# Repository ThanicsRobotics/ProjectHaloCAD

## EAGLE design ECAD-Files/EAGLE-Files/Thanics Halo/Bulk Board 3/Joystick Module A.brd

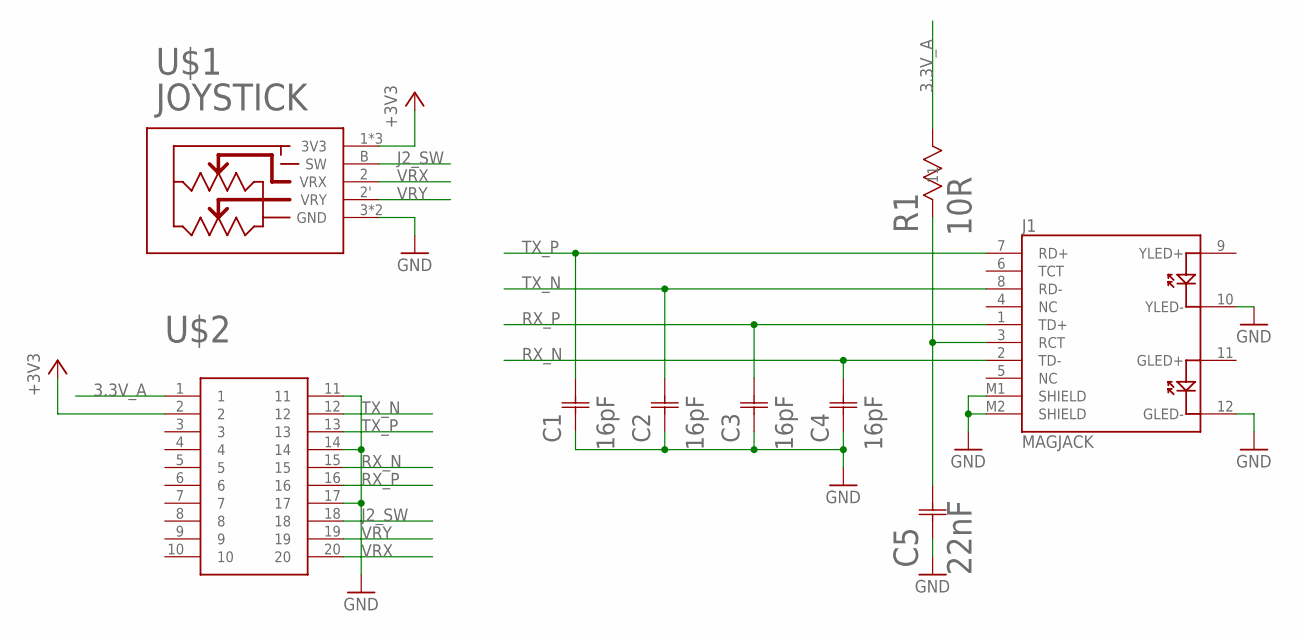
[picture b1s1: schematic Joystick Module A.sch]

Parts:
C1, C2, C3, C4: 16pF; G-155-M
C5: 22nF; G-155-M
J1: MAGJACK
R1: 10R; STA_RNCP0805-M
U$1: JOYSTICK"; JOYSTICK
U$2: EDGE_CONNECTOR_20POS_CONTACTS

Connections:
3.3V_A: R1.2 (22), U$2.1
+3V3: U$1.1 (3V3), U$1.1' (3V3), U$1.A (3V3), U$2.2
GND: C1.1 (11), C2.1 (11), C3.1 (11), C4.1 (11), C5.1 (11), J1.10 (YLED-), J1.12 (GLED-), J1.M1 (SHIELD), J1.M2 (SHIELD), U$1.3 (GND), U$1.3' (GND), U$2.11, U$2.14, U$2.17
J2_SW: U$1.B (SW), U$2.18
unnamed: C5.2 (22), J1.3 (RCT), R1.1 (11)
RX_N: C4.2 (22), J1.2 (TD-), U$2.15
RX_P: C3.2 (22), J1.1 (TD+), U$2.16
TX_N: C2.2 (22), J1.8 (RD-), U$2.12
TX_P: C1.2 (22), J1.7 (RD+), U$2.13
VRX: U$1.2 (VRX), U$2.20
VRY: U$1.2' (VRY), U$2.19

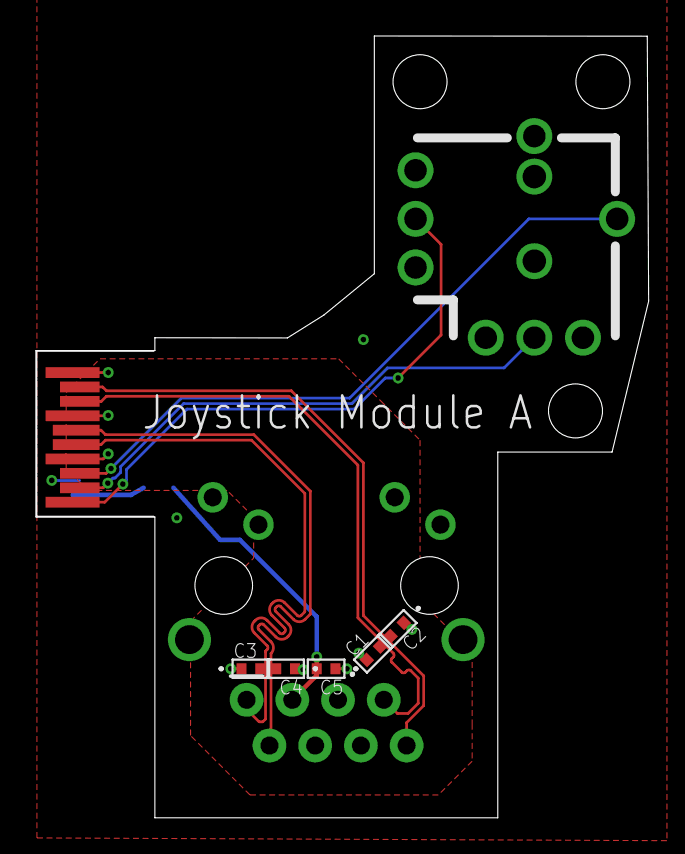
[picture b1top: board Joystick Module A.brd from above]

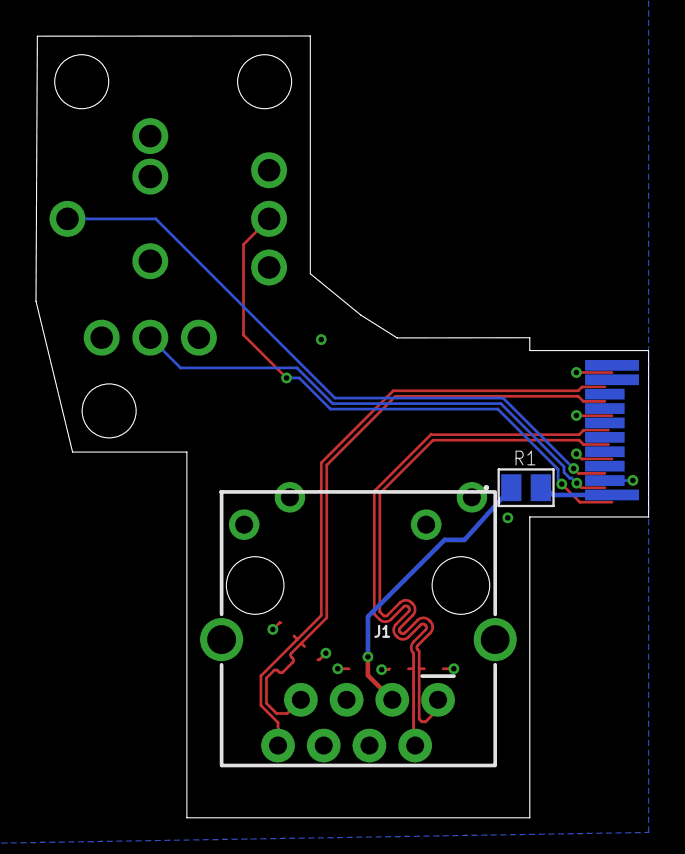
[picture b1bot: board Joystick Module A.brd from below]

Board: 4 copper layers, 34.0 x 43.4 mm, 9 parts (2 on the bottom side), 11 nets.

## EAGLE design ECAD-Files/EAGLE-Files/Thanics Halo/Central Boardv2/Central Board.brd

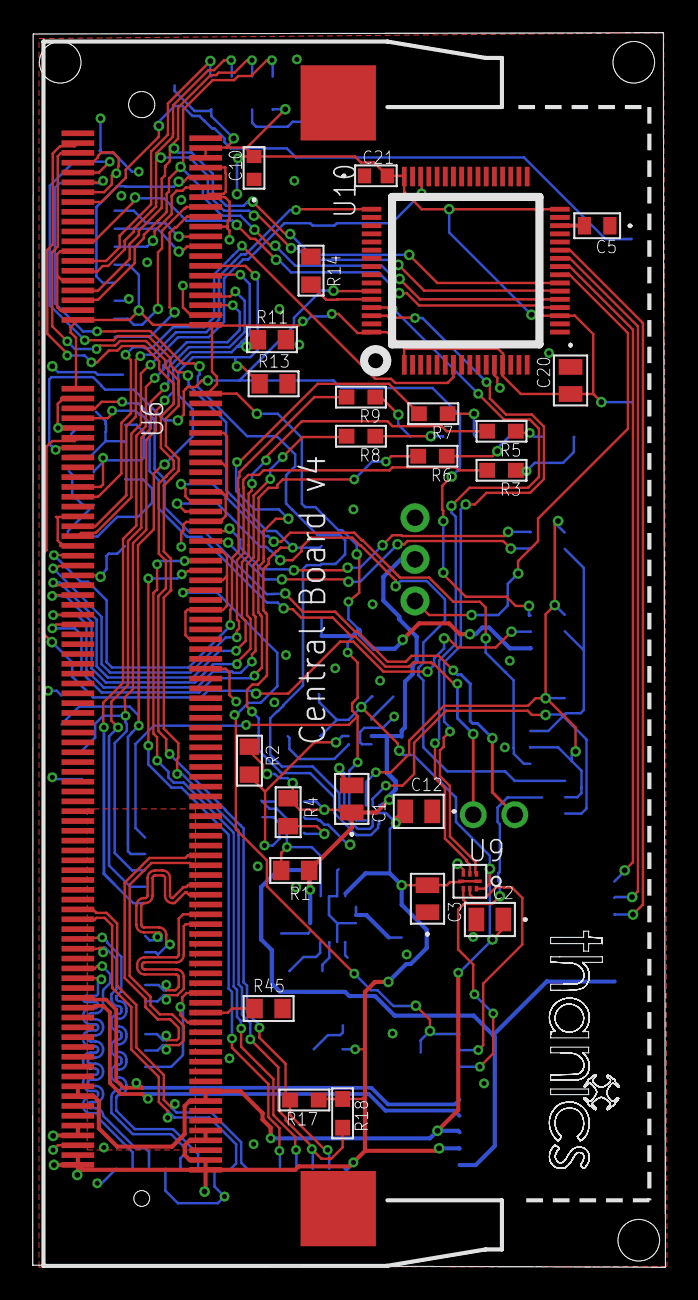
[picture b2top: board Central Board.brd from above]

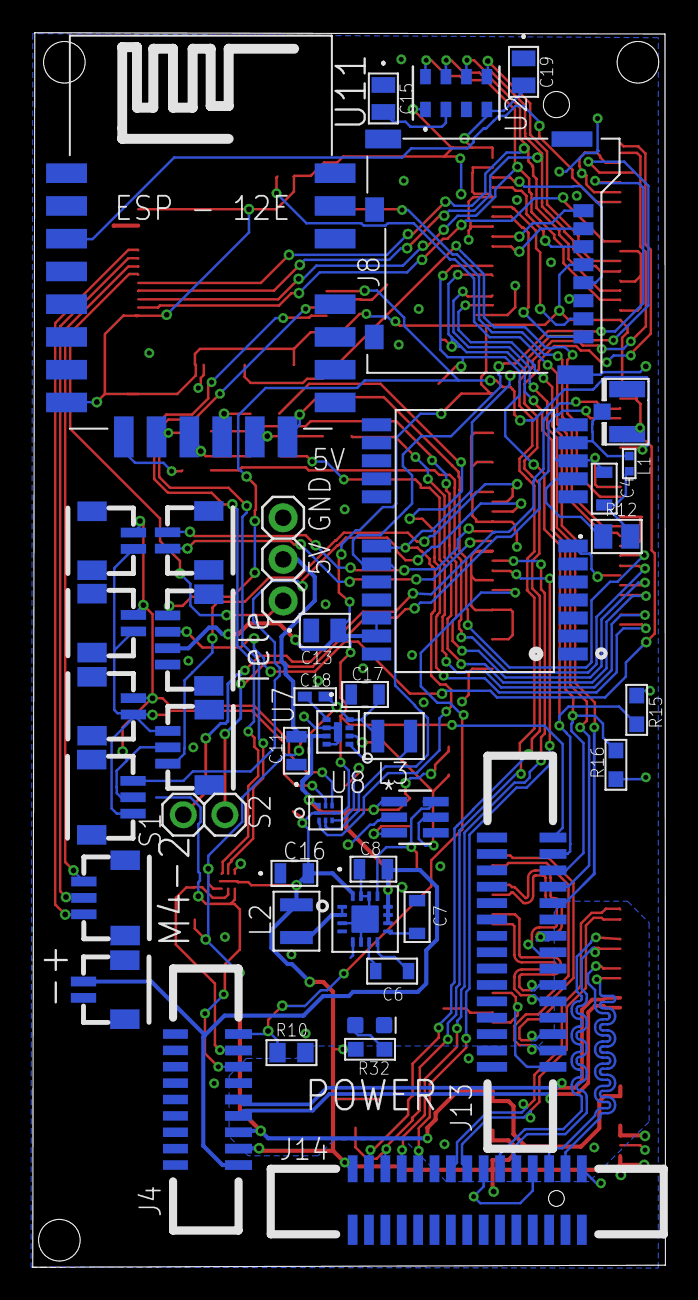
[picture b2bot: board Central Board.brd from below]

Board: 4 copper layers, 38.6 x 75.4 mm, 69 parts (43 on the bottom side), 91 nets.

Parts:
C1, C2, C3, C12, C13, C20: 0.1uF; 0805
C4, C6, C7: 10nF; 0603_CAPACITOR
C5: 4.7uF; 0603-M
C8, C11, C17: 10uF; G-21
C10, C21: 2.2uF; G-188-M
C15, C19: 1uF; YAG_CC0805
C16: 22uF; G-21
C18: 560pF; CC0402N-M
D1: GREEN; LED-0603
J1, J2, J6, J7, J9: JST_SH_2POS
J3: JST_SH_4POS
J4: 9POS_FFC_CONNECTOR
J5: U.FL
J8: MICROSD
J10, J11, J12: JST_SH_3POS
J13, J14: 15POS_FFC_CONNECTOR
JP1: 1X02
JP2: 1X03
L1: 27 nH; 0402_INDUCTOR
L2, L3: 470nH; 1008_INDUCTOR
R1, R2, R4, R10, R11, R13, R14, R45: 10k; RC0805N
R3, R5, R6, R7, R8, R9, R32: 20R; RC0603N-M
R12: 10; STA_RNCP0805-M
R15, R16, R17, R18: 1k; RC0603N-M
U2: LGA8-M
U3: LM3880MF-1AA/NOPBMF06A-M; MF06A-M
U4: NEO-M8
U5: TPS6209; VQFN16
U6: SO-DIMM
U7: MIC23050; MLF(ML)_8PIN
U8, U9: 8-UMLP
U10: LQFP64
U11: ESP12E-SMD

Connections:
1.8V: C2.1, C17.2, C18.2, J4.3, L3.P$2, U6.183, U6.184, U6.185, U6.186, U7.4, U9.8
+3V3: C3.2, C10.2, C12.2, C13.2, C16.2, C19.2, C20.2, C21.2, J3.3, J4.2, J8.4, J13.15, J14.15, L2.P$2, R15.1, R16.1, R17.1, R18.1, R32.2, U2.1, U2.4, U4.22, U4.23, U5.16, U6.4, U6.6, U6.39, U6.40, U6.41, U6.42, U6.191, U6.192, U6.193, U6.194, U6.197, U6.198, U6.199, U6.200, U8.1, U8.5, U9.1, U9.5, U10.1, U10.13, U10.19, U10.32, U10.48, U10.64, U11.VCC
+5V: C1.1, C8.2, C11.2, J4.1, J6.1, JP2.2, R1.1, R2.1, R4.1, U3.1, U5.10, U5.11, U5.12, U7.7, U8.8
C0_C_N: J13.8, U6.144
C0_C_P: J13.9, U6.142
C0_D0_N: J13.2, U6.138
C0_D0_P: J13.3, U6.136
C0_D1_N: J13.5, U6.150
C0_D1_P: J13.6, U6.148
C0_IO0: J13.11, U6.36
C0_IO1: J13.12, U6.34
C1_C_N: J14.8, U6.149
C1_C_P: J14.9, U6.147
C1_D0_N: J14.2, U6.161
C1_D0_P: J14.3, U6.159
C1_D1_N: J14.5, U6.155
C1_D1_P: J14.6, U6.153
C1_IO0: J14.11, U6.78
C1_IO1: J14.12, U6.76
GND: C1.2, C2.2, C3.1, C4.1, C5.1, C7.1, C8.1, C10.1, C11.1, C12.1, C13.1, C15.1, C16.1, C17.1, C19.1, C20.1, C21.1, D1.C, J3.4, J4.6, J5.P$1, J5.P$2, J6.2, J8.6, J8.9, J8.10, J8.11, J8.12, J8.13, J13.1, J13.4, J13.7, J13.10, J14.1, J14.4, J14.7, J14.10, JP2.3, R10.2, R11.2, R13.2, R14.1, R45.2, U2.3, U3.2, U4.7, U4.10, U4.12, U4.13, U4.24, U5.3, U5.5, U5.6, U5.14, U5.15, U5.17, U6.1, U6.7, U6.8, U6.13, U6.14, U6.19, U6.20, U6.25, U6.26, U6.31, U6.32, U6.37, U6.38, U6.43, U6.44, U6.49, U6.50, U6.55, U6.56, U6.61, U6.62, U6.67, U6.68, U6.73, U6.74, U6.79, U6.80, U6.85, U6.86, U6.91, U6.92, U6.97, U6.98, U6.103, U6.104, U6.109, U6.110, U6.115, U6.116, U6.121, U6.122, U6.127, U6.133, U6.134, U6.139, U6.140, U6.145, U6.146, U6.151, U6.152, U6.157, U6.163, U6.164, U6.169, U6.170, U6.181, U6.182, U6.187, U6.188, U6.195, U6.196, U6.G1, U6.G2, U7.6, U7.8, U7.EP, U8.4, U9.4, U10.12, U10.18, U10.31, U10.47, U10.63, U11.GND
GPCLK1: J4.9, R10.1, U6.82
I2C_MPU_SCL: U9.3, U10.61
I2C_MPU_SDA: U9.2, U10.62
I2C_SCL: U4.19, U6.11, U8.3
I2C_SCL_1V8: J4.7, U9.6
I2C_SCL_5V: J1.2, J2.2, J7.2, J10.2, J11.2, U8.6
I2C_SDA: U4.18, U6.9, U8.2
I2C_SDA_1V8: J4.8, U9.7
I2C_SDA_5V: J1.1, J2.1, J7.1, J10.1, J11.1, U8.7
ID_SD: U6.15, U11.CH_PD
INT_A: J10.3, U6.64
INT_B: J11.3, U6.66
MOTOR1: JP2.1, U10.24
MOTOR2: J12.1, U10.25
MOTOR3: J12.2, U10.26
MOTOR4: J12.3, U10.27
unnamed: J5.P$3, L1.P$1, U4.11
unnamed: C6.2, U5.7
unnamed: C6.1, U5.8
unnamed: D1.A, R32.1
unnamed: R1.2, U3.6, U5.13
unnamed: R2.2, U3.5, U7.2
unnamed: R3.1, U11.CS0
unnamed: R5.1, U11.MISO
unnamed: R6.1, U11.GPIO9
unnamed: R7.1, U11.GPIO10
unnamed: C5.2, U10.30
unnamed: C15.2, U2.2
unnamed: R12.1, U4.9
unnamed: R8.1, U11.MOSI
unnamed: R9.1, U11.SCLK
unnamed: R14.2, U10.60
unnamed: C4.2, L1.P$2, R12.2
unnamed: C7.2, U5.9
unnamed: L2.P$1, U5.1, U5.2
unnamed: L3.P$1, U7.1
unnamed: C18.1, U7.5
unnamed: R45.1, U6.168
NRST: U6.63, U10.7
POWER_SEQ_EN: R4.2, U3.3
SCL0: J13.13, R11.1, R16.2, U6.30
SCL1: J14.13, R18.2, U6.5
SDA0: J13.14, R13.1, R15.2, U6.28
SDA1: J14.14, R17.2, U6.3
SDX_CLK: J8.5, U6.10
SDX_CMD: J8.3, U6.12
SDX_D0: J8.7, U6.16
SDX_D1: J8.8, U6.18
SDX_D2: J8.1, U6.22
SDX_D3: J8.2, U6.24
SD_CLK: R9.2, U6.75
SD_CMD: R3.2, U6.77
SD_D0: R5.2, U6.81
SD_D1: R8.2, U6.83
SD_D2: R6.2, U6.87
SD_D3: R7.2, U6.89
SERVO1: JP1.1, U6.45
SERVO2: JP1.2, U6.47
SPI_CS0: U2.5, U6.27
SPI_CS1: U6.23, U10.20
SPI_MISO: U2.6, U6.29, U10.22
SPI_MOSI: U2.7, U6.33, U10.23
SPI_SCLK: U2.8, U6.35, U10.21
SWCLK: U6.69, U10.49
SWDIO: U6.71, U10.46
UART2_RX: J9.2, U6.72
UART2_TX: J9.1, U6.70
USART1_RX: J3.1, U6.53, U10.59
USART1_TX: J3.2, U6.51
USB_D_N: J4.4, U6.167
USB_D_P: J4.5, U6.165

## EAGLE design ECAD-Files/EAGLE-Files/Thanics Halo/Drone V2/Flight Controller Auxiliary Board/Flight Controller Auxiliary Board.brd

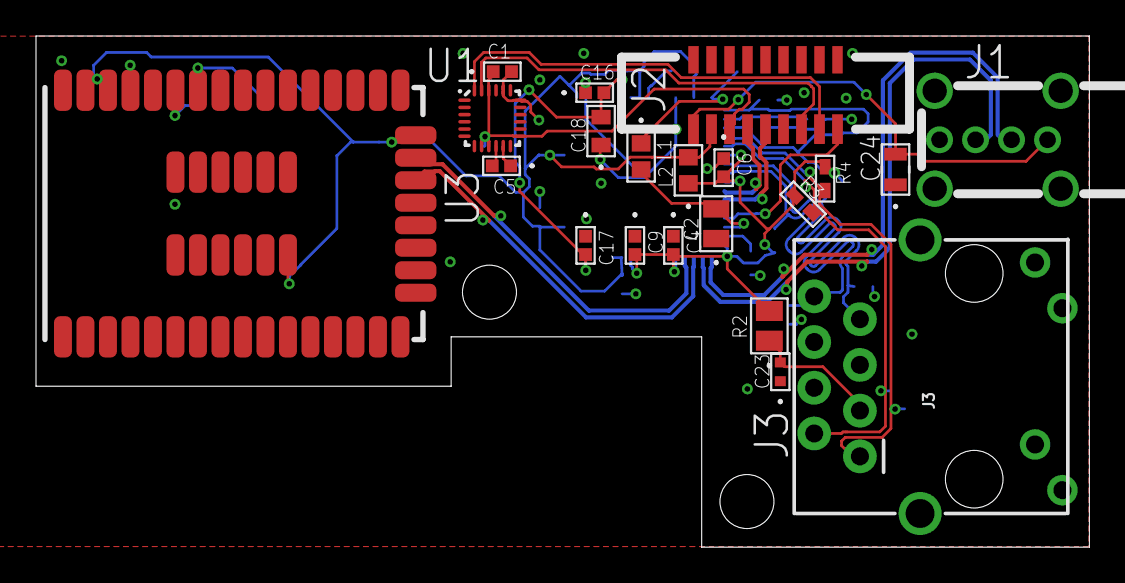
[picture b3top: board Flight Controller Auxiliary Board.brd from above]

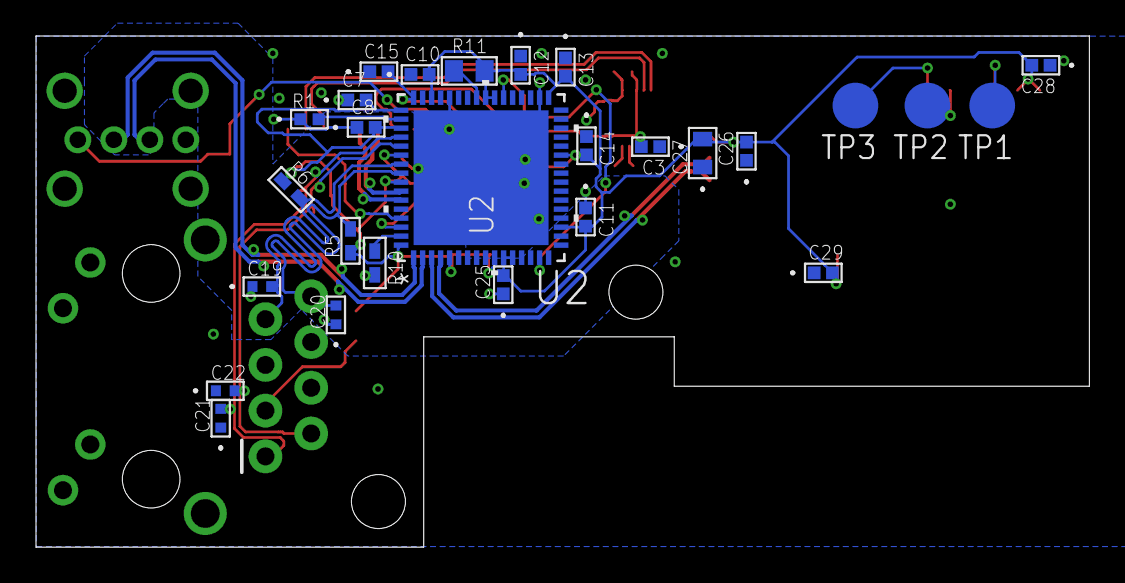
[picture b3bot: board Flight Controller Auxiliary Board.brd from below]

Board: 4 copper layers, 58.5 x 28.4 mm, 48 parts (27 on the bottom side), 29 nets.

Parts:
C1, C3, C4, C5, C6, C7, C8, C9, C10, C11, C12, C13, C14, C15, C16, C17, C25, C26, C28, C29: 0.1uF; 0402-M
C2: 1uF; YAG_CC0805
C18, C27: 4.7uF; 0603-M
C19, C20, C21, C22: 16pF; G-155-M
C23: 22nF; G-155-M
C24: 22uF; G-21
J1: USB_A_VERTICAL
J2: 9POS_FFC_CONNECTOR
J3: MAGJACK
L1, L2: FB; IND_BLM18_0603-M
R1: 12.4k; YAG_R0402-M
R2: 10R; STA_RNCP0805-M
R3, R4, R5, R6: 49R9; RC0402N-M
R10: 12k; RC0402N-M
R11: 10k; RC0805N
TP1, TP2, TP3: TPB2,54; B2,54
U1: QFN40P300X300X105-25N
U2: QFN64_9X9MC-M
U3: WGM110A

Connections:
1.8V: C1.1, C3.2, J2.3, U1.8, U1.9, U1.13, U1.22
3.3V_A: C4.2, C6.2, C7.2, C8.2, C9.2, L2.1, R2.2, R3.1, R4.1, R5.1, R6.1, U2.5, U2.10, U2.49, U2.51, U2.54, U2.57, U2.64
+3V3: C10.2, C11.2, C12.2, C13.2, C14.2, C25.2, C26.2, C27.2, C28.2, C29.2, J2.2, L2.2, R11.2, U2.11, U2.12, U2.19, U2.27, U2.33, U2.39, U2.40, U2.46, U3.24, U3.38, U3.39, U3.51
+5V: C24.2, J1.1, J2.1
GND: C1.2, C2.1, C3.1, C4.1, C5.1, C6.1, C7.1, C8.1, C9.1, C10.1, C11.1, C12.1, C13.1, C14.1, C15.1, C16.1, C17.1, C18.1, C19.1, C20.1, C21.1, C22.1, C23.1, C24.1, C25.1, C26.1, C27.1, C28.1, C29.1, J1.4, J1.P$5, J1.P$6, J1.P$7, J1.P$8, J2.6, J3.10, J3.12, J3.M1, J3.M2, R1.1, R10.2, U1.11, U1.18, U1.20, U2.34, U2.44, U2.65, U3.1, U3.16, U3.25, U3.40, U3.42, U3.44, U3.46, U3.48
GPCLK: J2.9, U2.61
unnamed: R11.1, U2.41
unnamed: R10.1, U2.63
unnamed: C15.2, L1.1, U2.48
unnamed: C2.2, L1.2, U2.62
unnamed: TP1.TP, U3.37
unnamed: TP2.TP, U3.35
unnamed: TP3.TP, U3.34
unnamed: C5.2, U1.10
unnamed: R1.2, U2.50
unnamed: C16.2, C17.2, C18.2, U2.15, U2.38
unnamed: C23.2, J3.3, R2.1
RX_N: C22.2, J3.2, R3.2, U2.53
RX_P: C21.2, J3.1, R4.2, U2.52
SCL: J2.7, U1.23
SDA: J2.8, U1.24
TX_N: C20.2, J3.8, R5.2, U2.56
TX_P: C19.2, J3.7, R6.2, U2.55
USB_D2_N: J1.2, U2.1
USB_D2_P: J1.3, U2.2
USB_D3_N: U2.3, U3.22
USB_D3_P: U2.4, U3.23
USB_D_N: J2.4, U2.58
USB_D_P: J2.5, U2.59

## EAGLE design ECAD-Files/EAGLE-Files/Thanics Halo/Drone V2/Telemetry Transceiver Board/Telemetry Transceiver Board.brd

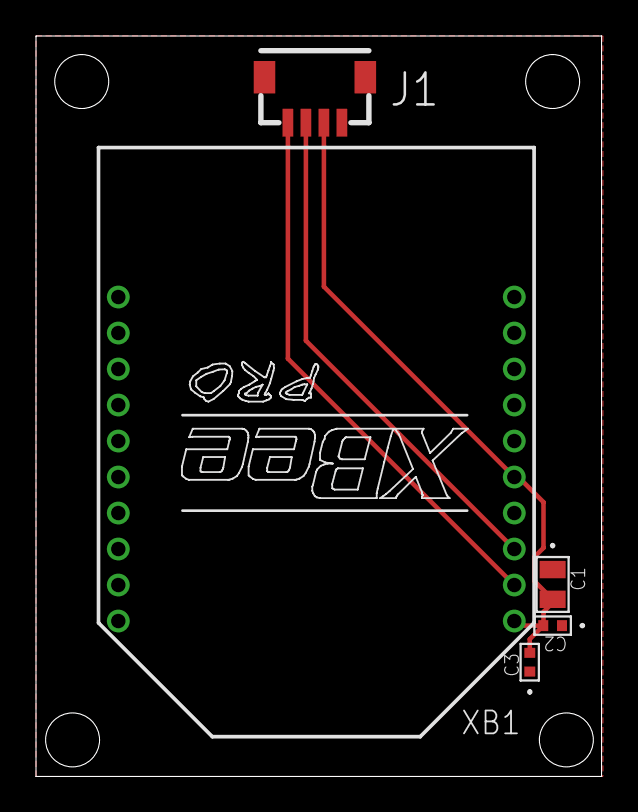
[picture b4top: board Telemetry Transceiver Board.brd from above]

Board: 2 copper layers, 31.4 x 41.1 mm, 5 parts (0 on the bottom side), 4 nets.

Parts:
C1: 1uF; YAG_CC0805
C2, C3: 16pF; G-155-M
J1: JST_SH_4POS
XB1: XBEE-PRO

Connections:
+3V3: C1.2, C2.2, C3.2, J1.3, XB1.1, XB1.5
GND: C1.1, C2.1, C3.1, J1.4, XB1.10, XB1.14
RX: J1.2, XB1.3
TX: J1.1, XB1.2

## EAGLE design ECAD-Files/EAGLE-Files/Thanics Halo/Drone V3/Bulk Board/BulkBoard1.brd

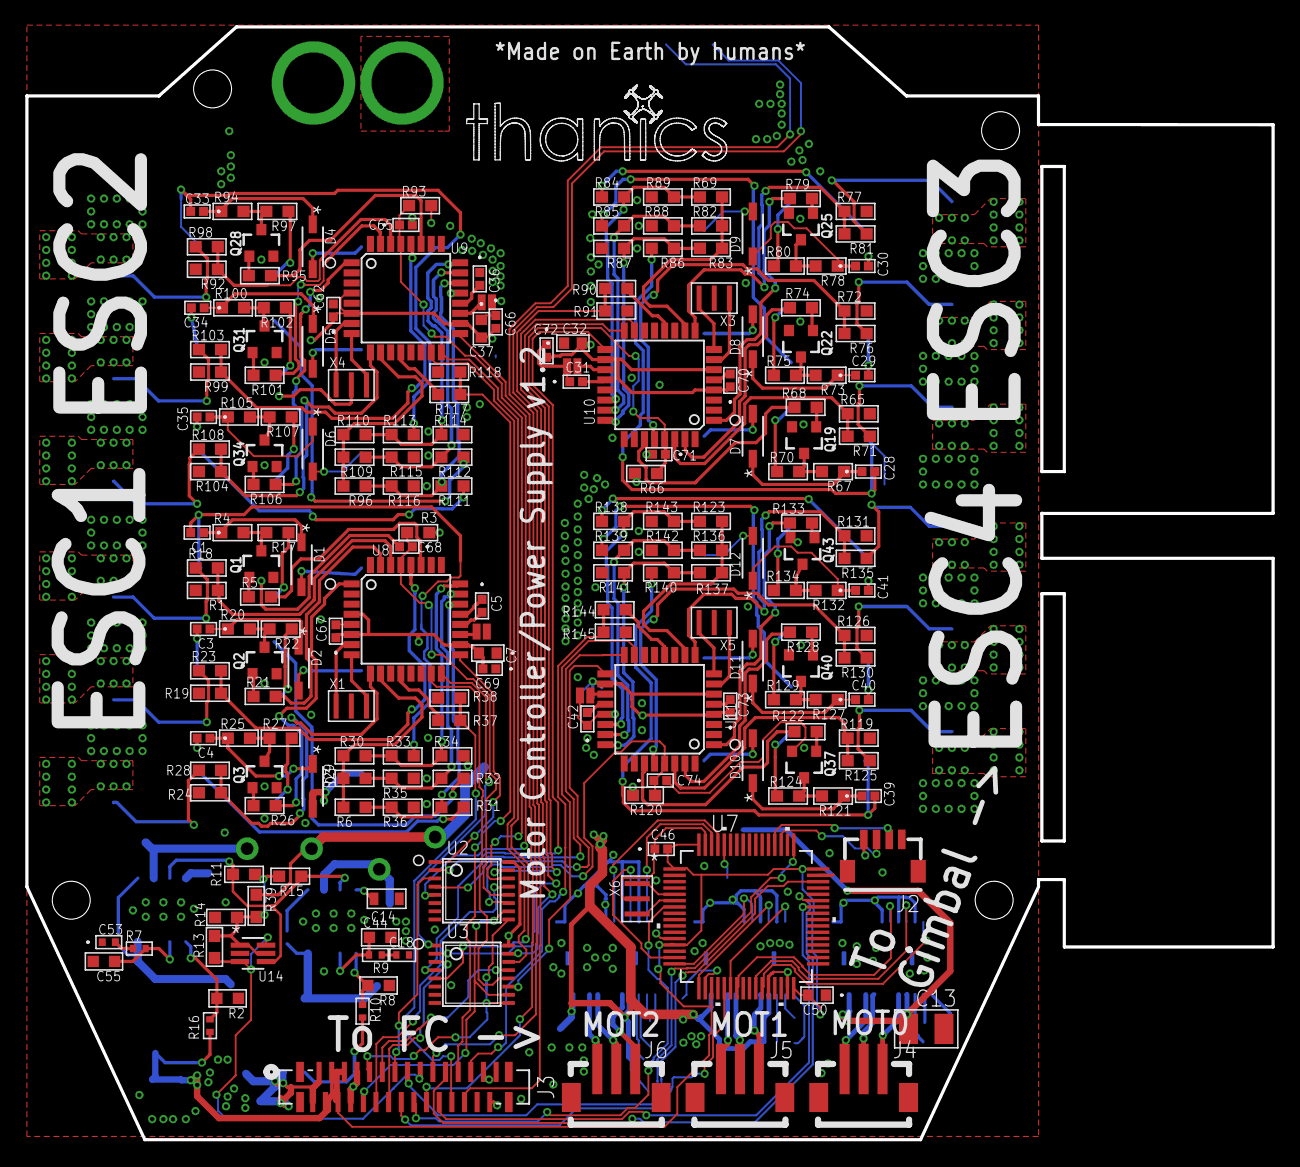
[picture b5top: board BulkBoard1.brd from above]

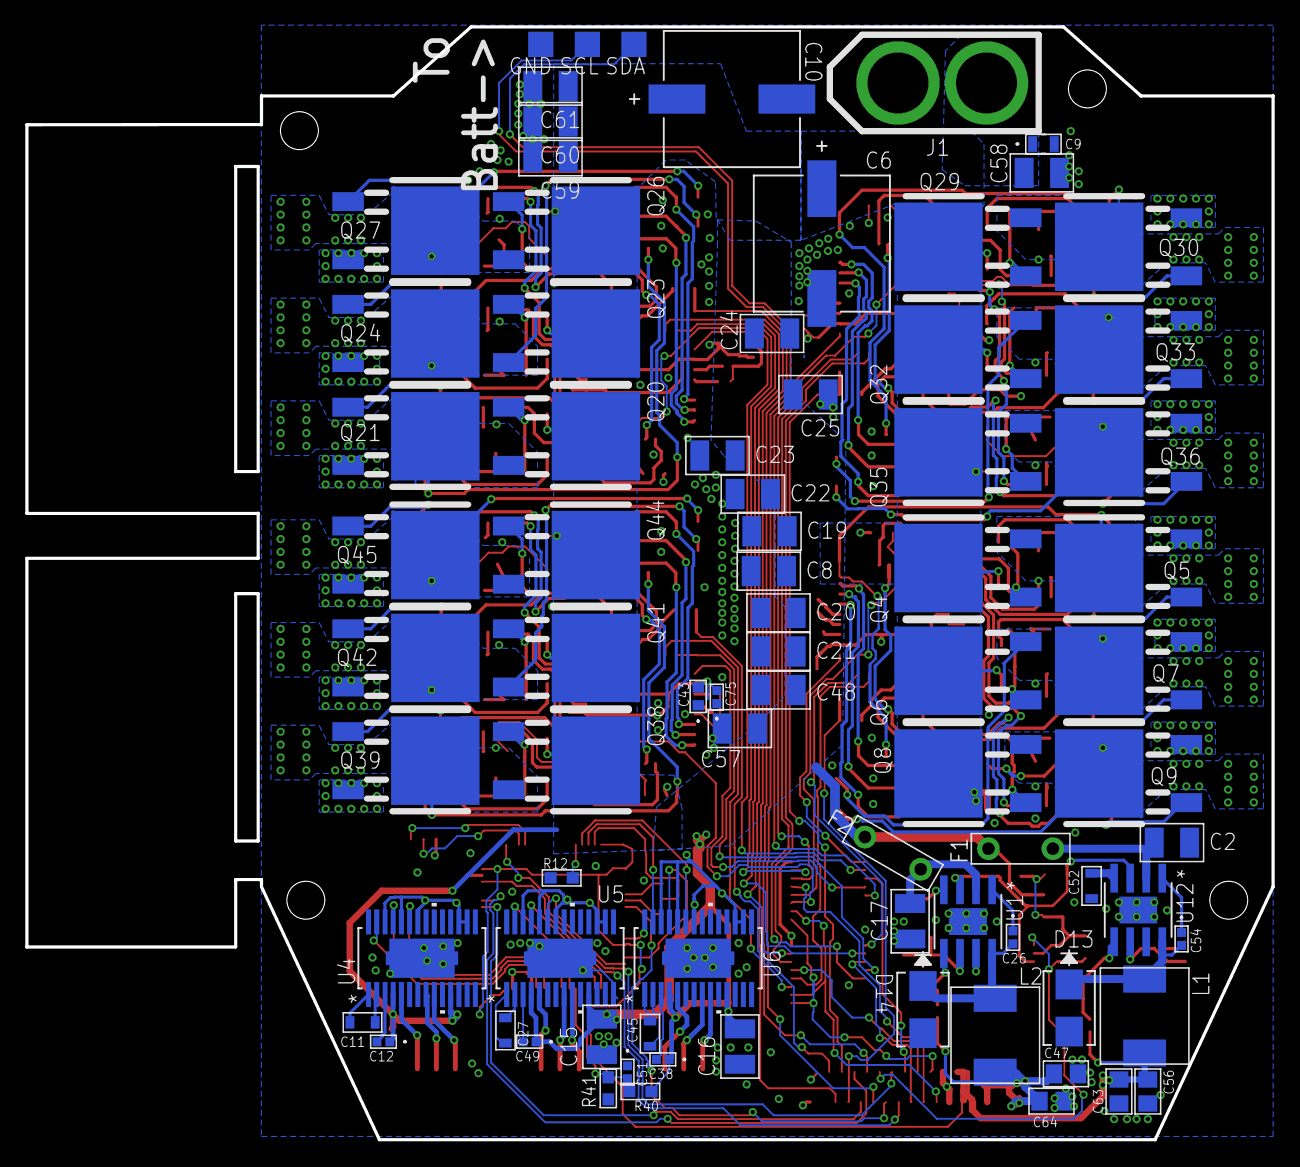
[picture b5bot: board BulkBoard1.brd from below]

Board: 4 copper layers, 98.6 x 88.0 mm, 282 parts (79 on the bottom side), 219 nets.

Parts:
C1, C3, C4, C28, C29, C30, C33, C34, C35, C39, C40, C41: 0.1uF (50V); 0402-M
C2, C8, C13, C15, C16, C17, C19, C20, C21, C22, C23, C24, C25, C48, C57, C58, C59, C60, C61: 22uF; 1210_CAPACITOR
C5, C12, C26, C31, C36, C38, C42, C46, C49, C51, C54, C62, C65, C66, C67, C68, C69, C70, C71, C72, C73, C74, C75: 0.1uF; 0402-M
C6, C10: 470uF; PCAP_10X10-ELECT-M
C7, C32, C37, C43, C50: 2.2uF; G-188-M
C9: 10uF; G-21
C11, C14, C27, C45, C52: 10nF; 0603_CAPACITOR
C18: 1nF; C0402
C44, C55: 43pF; C0603
C47, C56, C63, C64: 22uF; C0805
C53: 2.2nF; 0402_CAPACITOR
D1, D2, D3, D4, D5, D6, D7, D8, D9, D10, D11, D12: 1N4148; SOD123-M
D13, D14: SSB44-E3/52T; DIODE_DO214AA_MBRS-M
F1, F2: 0ZRB0400FF1A
GND: TPTP20SQ; TP20SQ
J1: ESC_CONTACTS; XT60_CONNECTOR
J2: JST_SH_4POS
J3: 62674-301121ALF; CON30_1X30_DUT_58XF
J4, J5, J6: B3B-ZR-SM4
JP1, JP3, JP4, JP5: JUMPER-SMT_2_NO_NO-SILK; SMT-JUMPER_2_NO_NO-SILK
L1, L2: 10uH; PA431.XXX
Q1, Q2, Q3, Q19, Q22, Q25, Q28, Q31, Q34, Q37, Q40, Q43: 500mA/300V; SOT23-3
Q4, Q5, Q6, Q7, Q8, Q9, Q20, Q21, Q23, Q24, Q26, Q27, Q29, Q30, Q32, Q33, Q35, Q36, Q38, Q39, Q41, Q42, Q44, Q45: IRLR8726; DPAK
R1, R3, R12, R19, R24, R37, R38, R40, R65, R66, R72, R77, R90, R91, R92, R93, R99, R104, R117, R118, R119, R120, R126, R131, R144, R145: 10k; RC0603N-M
R2: 3.24k; R0603
R4, R20, R25, R39, R67, R73, R78, R94, R100, R105, R121, R127, R132: 2.2k; RC0603N-M
R5, R21, R26, R34, R35, R36, R68, R74, R79, R87, R88, R89, R95, R101, R106, R114, R115, R116, R122, R128, R133, R141, R142, R143: 4.7k; RC0603N-M
R6, R29, R30, R31, R32, R33, R69, R82, R83, R84, R85, R86, R96, R109, R110, R111, R112, R113, R123, R136, R137, R138, R139, R140: 47k; RC0603N-M
R7: 28.7k; R0402
R8: 1.96k; R0603
R9: 39.2k; R0402
R10, R16: 10.2k; R0402
R11, R13, R15: 100k; RC0603N-M
R14: 1k; RC0603N-M
R17, R18, R22, R23, R27, R28, R70, R71, R75, R76, R80, R81, R97, R98, R102, R103, R107, R108, R124, R125, R129, R130, R134, R135: 100R; RC0603N-M
R41: 1.5k; RC0603N-M
SCL: TPTP20SQ; TP20SQ
SDA: TPTP20SQ; TP20SQ
U1, U12: TPS54331DRD8-M; D8-M
U2, U3: 74HC4052PW; TSSOP16
U4, U5, U6: DRV8313; PWP28_5P18X3P1-M
U7: STM32F103RCT6LQFP-64-M; LQFP-64-M
U8, U9, U10, U11: MEGA8-AI; TQFP32-08
U14: SN74LVC1G373DCKRDCK6-M; DCK6-M
X1, X3, X4, X5: 16MHz; 3-SMD
X6: 8MHz; 3-SMD

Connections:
+3V3: C46.2, C50.2, C56.1, C63.1, J3.3, J3.4, J3.5, J3.6, L1.P$2, R16.2, U7.1, U7.13, U7.19, U7.32, U7.48, U7.64
+5V: C7.2, C32.2, C37.2, C43.2, C47.1, C62.1, C64.1, C66.2, C67.1, C69.2, C70.1, C72.2, C73.1, C75.2, J2.4, J3.1, J3.2, L2.P$2, R3.2, R10.2, R66.2, R93.2, R120.2, U2.16, U3.16, U4.16, U4.17, U4.22, U4.24, U4.26, U5.16, U5.17, U5.22, U5.24, U5.26, U6.16, U6.17, U6.22, U6.24, U6.26, U8.4, U8.6, U8.18, U9.4, U9.6, U9.18, U10.4, U10.6, U10.18, U11.4, U11.6, U11.18
A0: U4.27, U7.27
A1: U5.27, U7.22
A2: U6.27, U7.62
AHIN: R5.2, U8.27
AHIN2: R95.2, U9.27
AHIN3: R68.2, U10.27
AHIN4: R122.2, U11.27
ALIN: R1.1, R18.2, U8.30
ALIN2: R92.1, R98.2, U9.30
ALIN3: R65.1, R71.2, U10.30
ALIN4: R119.1, R125.2, U11.30
AOUT: C1.2, Q4.3, Q5.2, R33.1
AOUT2: C33.2, Q29.3, Q30.2, R113.1
AOUT3: C28.2, Q20.3, Q21.2, R86.1
AOUT4: C39.2, Q38.3, Q39.2, R140.1
A_SENSE: R30.1, R33.2, R34.1, U8.24
A_SENSE2: R110.1, R113.2, R114.1, U9.24
A_SENSE3: R83.1, R86.2, R87.1, U10.24
A_SENSE4: R137.1, R140.2, R141.1, U11.24
B0: U4.25, U7.26
B1: U5.25, U7.17
B2: U6.25, U7.15
BATT_SCL: J3.20, SCL.TP
BATT_SDA: J3.19, SDA.TP
BHIN: R21.2, U8.31
BHIN2: R101.2, U9.31
BHIN3: R74.2, U10.31
BHIN4: R128.2, U11.31
BLIN: R19.1, R23.2, U8.28
BLIN2: R99.1, R103.2, U9.28
BLIN3: R72.1, R76.2, U10.28
BLIN4: R126.1, R130.2, U11.28
BOOT0: R12.2, U7.60
BOUT: C3.2, Q6.3, Q7.2, R32.1
BOUT2: C34.2, Q32.3, Q33.2, R112.1
BOUT3: C29.2, Q23.3, Q24.2, R85.1
BOUT4: C40.2, Q41.3, Q42.2, R139.1
B_SENSE: R29.1, R32.2, R35.1, U8.23
B_SENSE2: R109.1, R112.2, R115.1, U9.23
B_SENSE3: R82.1, R85.2, R88.1, U10.23
B_SENSE4: R136.1, R139.2, R142.1, U11.23
C0: U4.23, U7.23
C1: U5.23, U7.16
C2: U6.23, U7.61
CHIN: R26.2, U8.1
CHIN2: R106.2, U9.1
CHIN3: R79.2, U10.1
CHIN4: R133.2, U11.1
CLIN: R24.1, R28.2, U8.9
CLIN2: R104.1, R108.2, U9.9
CLIN3: R77.1, R81.2, U10.9
CLIN4: R131.1, R135.2, U11.9
COUT: C4.2, Q8.3, Q9.2, R31.1
COUT2: C35.2, Q35.3, Q36.2, R111.1
COUT3: C30.2, Q26.3, Q27.2, R84.1
COUT4: C41.2, Q44.3, Q45.2, R138.1
C_SENSE: R6.1, R31.2, R36.1, U8.22
C_SENSE2: R96.1, R111.2, R116.1, U9.22
C_SENSE3: R69.1, R84.2, R89.1, U10.22
C_SENSE4: R123.1, R138.2, R143.1, U11.22
EN: R11.2, R15.1, U1.3, U12.3, U14.4
GND: C2.2, C5.1, C6.2, C7.1, C8.1, C9.2, C10.2, C13.1, C14.1, C15.1, C16.1, C17.2, C18.2, C19.1, C20.1, C21.1, C22.1, C23.1, C24.1, C25.1, C31.1, C32.1, C36.1, C37.1, C42.1, C43.1, C44.2, C46.1, C47.2, C48.2, C50.1, C51.1, C52.1, C53.1, C55.2, C56.2, C57.2, C58.2, C59.2, C60.2, C61.2, C62.2, C63.2, C64.2, C65.2, C66.1, C67.2, C68.2, C69.1, C70.2, C71.2, C72.1, C73.2, C74.2, C75.1, D13.2, D14.2, GND.TP, J1.-, J2.1, J3.7, J3.8, J3.27, J3.28, J3.29, J3.30, JP1.2, JP3.2, JP4.2, JP5.2, Q1.2, Q2.2, Q3.2, Q5.3, Q7.3, Q9.3, Q19.2, Q21.3, Q22.2, Q24.3, Q25.2, Q27.3, Q28.2, Q30.3, Q31.2, Q33.3, Q34.2, Q36.3, Q37.2, Q39.3, Q40.2, Q42.3, Q43.2, Q45.3, R1.2, R2.1, R8.1, R12.1, R14.2, R19.2, R24.2, R34.2, R35.2, R36.2, R38.2, R41.2, R65.2, R72.2, R77.2, R87.2, R88.2, R89.2, R91.2, R92.2, R99.2, R104.2, R114.2, R115.2, R116.2, R118.2, R119.2, R126.2, R131.2, R141.2, R142.2, R143.2, R145.2, U1.7, U1.EP, U2.6, U2.7, U2.8, U3.6, U3.7, U3.8, U4.6, U4.7, U4.10, U4.14, U4.20, U4.28, U4.29, U5.6, U5.7, U5.10, U5.14, U5.20, U5.28, U5.29, U6.6, U6.7, U6.10, U6.14, U6.20, U6.28, U6.29, U7.12, U7.18, U7.28, U7.31, U7.47, U7.63, U8.3, U8.5, U8.21, U9.3, U9.5, U9.21, U10.3, U10.5, U10.21, U11.3, U11.5, U11.21, U12.7, U12.EP, U14.2, X1.2, X3.2, X4.2, X5.2, X6.2
LIPO: C51.2, R40.2, R41.1, U7.21
MISO: J3.13, U3.3
MISO1: U3.1, U8.16
MISO2: U3.5, U9.16
MISO3: U3.2, U10.16
MISO4: U3.4, U11.16
MOSI: J3.12, U3.13
MOSI1: U3.12, U8.15
MOSI2: U3.14, U9.15
MOSI3: U3.15, U10.15
MOSI4: U3.11, U11.15
MOT0_1: J4.1, U4.5
MOT0_2: J4.2, U4.8
MOT0_3: J4.3, U4.9
MOT1_1: J5.1, U5.5
MOT1_2: J5.2, U5.8
MOT1_3: J5.3, U5.9
MOT2_1: J6.1, U6.5
MOT2_2: J6.2, U6.8
MOT2_3: J6.3, U6.9
unnamed: C11.1, U4.2
unnamed: C55.1, R7.2, U12.6
unnamed: C53.2, R7.1
unnamed: Q1.1, R5.1
unnamed: Q4.1, R17.1
unnamed: Q1.3, R4.2, R17.2
unnamed: Q2.1, R21.1
unnamed: C1.1, D1.C, R4.1
unnamed: Q5.1, R18.1
unnamed: Q6.1, R22.1
unnamed: C52.2, U12.4
unnamed: C54.1, U12.1
unnamed: C44.1, R9.2, U1.6
unnamed: C18.1, R9.1
unnamed: C14.2, U1.4
unnamed: C26.1, U1.1
unnamed: C26.2, D14.1, L2.P$1, U1.8
unnamed: C54.2, D13.1, L1.P$1, U12.8
unnamed: R8.2, R10.1, U1.5
unnamed: R2.2, R16.1, U12.5
unnamed: Q2.3, R20.2, R22.2
unnamed: C3.1, D2.C, R20.1
unnamed: Q7.1, R23.1
unnamed: Q3.1, R26.1
unnamed: Q8.1, R27.1
unnamed: Q3.3, R25.2, R27.2
unnamed: C4.1, D3.C, R25.1
unnamed: Q9.1, R28.1
unnamed: C5.2, U8.20
unnamed: U8.7, X1.3
unnamed: U8.8, X1.1
unnamed: C11.2, U4.1
unnamed: JP1.1, U8.19
unnamed: C27.1, U5.2
unnamed: C27.2, U5.1
unnamed: C49.2, U5.3
unnamed: C45.1, U6.2
unnamed: C45.2, U6.1
unnamed: R37.2, U8.12
unnamed: C38.2, U6.3
unnamed: U7.5, X6.3
unnamed: C12.2, U4.3
unnamed: U7.6, X6.1
unnamed: Q19.1, R68.1
unnamed: Q20.1, R70.1
unnamed: Q19.3, R67.2, R70.2
unnamed: C28.1, D7.C, R67.1
unnamed: Q21.1, R71.1
unnamed: Q22.1, R74.1
unnamed: Q23.1, R75.1
unnamed: Q22.3, R73.2, R75.2
unnamed: C29.1, D8.C, R73.1
unnamed: Q24.1, R76.1
unnamed: Q25.1, R79.1
unnamed: Q26.1, R80.1
unnamed: Q25.3, R78.2, R80.2
unnamed: C30.1, D9.C, R78.1
unnamed: Q27.1, R81.1
unnamed: R90.2, U10.12
unnamed: JP3.1, U10.19
unnamed: C31.2, U10.20
unnamed: U10.7, X3.3
unnamed: U10.8, X3.1
unnamed: Q28.1, R95.1
unnamed: Q29.1, R97.1
unnamed: Q28.3, R94.2, R97.2
unnamed: C33.1, D4.C, R94.1
unnamed: Q30.1, R98.1
unnamed: Q31.1, R101.1
unnamed: Q32.1, R102.1
unnamed: Q31.3, R100.2, R102.2
unnamed: C34.1, D5.C, R100.1
unnamed: Q33.1, R103.1
unnamed: Q34.1, R106.1
unnamed: Q35.1, R107.1
unnamed: Q34.3, R105.2, R107.2
unnamed: C35.1, D6.C, R105.1
unnamed: Q36.1, R108.1
unnamed: R117.2, U9.12
unnamed: JP4.1, U9.19
unnamed: C36.2, U9.20
unnamed: U9.7, X4.3
unnamed: U9.8, X4.1
unnamed: Q37.1, R122.1
unnamed: Q38.1, R124.1
unnamed: Q37.3, R121.2, R124.2
unnamed: C39.1, D10.C, R121.1
unnamed: Q39.1, R125.1
unnamed: Q40.1, R128.1
unnamed: Q41.1, R129.1
unnamed: Q40.3, R127.2, R129.2
unnamed: C40.1, D11.C, R127.1
unnamed: Q42.1, R130.1
unnamed: Q43.1, R133.1
unnamed: Q44.1, R134.1
unnamed: Q43.3, R132.2, R134.2
unnamed: C41.1, D12.C, R132.1
unnamed: Q45.1, R135.1
unnamed: R144.2, U11.12
unnamed: JP5.1, U11.19
unnamed: C42.2, U11.20
unnamed: U11.7, X5.3
unnamed: U11.8, X5.1
NEUTRAL_SENSE: R6.2, R29.2, R30.2, U8.10
NEUTRAL_SENSE2: R96.2, R109.2, R110.2, U9.10
NEUTRAL_SENSE3: R69.2, R82.2, R83.2, U10.10
NEUTRAL_SENSE4: R123.2, R136.2, R137.2, U11.10
NT-RX: J2.2, U7.52
NT-TX: J2.3, U7.51
PWM: J3.23, R37.1, R38.1
PWM2: J3.24, R117.1, R118.1
PWM3: J3.25, R90.1, R91.1
PWM4: J3.26, R144.1, R145.1
PWR_EN: J3.18, R13.2, U14.3, U14.6
RESET: J3.17, U7.7
RST: J3.11, U2.13
RST1: C68.1, R3.1, U2.12, U8.29
RST2: C65.1, R93.1, U2.14, U9.29
RST3: C71.1, R66.1, U2.15, U10.29
RST4: C74.1, R120.1, U2.11, U11.29
RX: J3.22, U7.43
SCK: J3.14, U2.3
SCK1: U2.1, U8.17
SCK2: U2.5, U9.17
SCK3: U2.2, U10.17
SCK4: U2.4, U11.17
SEL0: J3.9, U2.10, U3.10
SEL1: J3.10, U2.9, U3.9
SWCLK: J3.16, U7.49
SWDIO: J3.15, U7.46
TX: J3.21, U7.42
V2FUSED: C17.1, F2.2, U1.2
VDD: C6.1, C8.2, C9.1, C10.1, C12.1, C13.2, C15.2, C16.2, C19.2, C20.2, C21.2, C22.2, C23.2, C24.2, C25.2, C38.1, C48.1, C49.1, C57.1, C58.1, C59.1, C60.1, C61.1, D1.A, D2.A, D3.A, D4.A, D5.A, D6.A, D7.A, D8.A, D9.A, D10.A, D11.A, D12.A, F1.1, F2.1, J1.+, Q4.2, Q6.2, Q8.2, Q20.2, Q23.2, Q26.2, Q29.2, Q32.2, Q35.2, Q38.2, Q41.2, Q44.2, R39.1, R40.1, U4.4, U4.11, U5.4, U5.11, U6.4, U6.11
VFUSED: C2.1, F1.2, U12.2
V_LATCH: R11.1, R13.1, R14.1, R15.2, R39.2, U14.1, U14.5

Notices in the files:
parts and their libraries:
SparkFun-Connectors: Licensing: Creative Commons ShareAlike 4.0 International - https://creativecommons.org/licenses/by-sa/4.0
COPYRIGHT: Copyright C 2015 Accelerated Designs. All rights reserved
